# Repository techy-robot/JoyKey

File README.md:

---
modified: 2025-02-20T21:09:22-07:00
---
# JoyKey
This is a small macropad that simultaneously acts as game controller and an entertainment device. 

The name is inspired by the Nintendo JoyCon portmanteau (Joystick Controller) except I have replaced the 2nd word with "Keypad" (Joystick Keypad). See [name ideas](name%20ideas.md) for other things I came up with.

My main repo were development will continue: https://github.com/techy-robot/JoyKey

# Features
- Customizable macro pad using QMK firmware
- Game controller mimicking a joy-con
- Offline games that can be played on the display with no connections
- Small handheld size
- Linear keys

# Approoved Parts BOM
- 8 Cherry mx Red keys with clear shell variant
- 8 Black keycaps
- 128x64 px SSD1306-based monochrome display near the top
- SEEED Xiao RP2040 (can be replaced later w/ SEEED xiao MG24 or nRF52840 Sense for BLE and other goodies)
- 12 Sk6812 Mini-E reverse mount RGB leds
- 3 M3x16 screws and M3 heatsets

# Extra Parts BOM
- 1 Analog PS2 Joystick (I already have)
- 1 Alps SRBE110301. (flat volume dial on the side). LCSC #C160861
- AP2112K-3.3 Linear Regulator. LCSC #C51118
- MCP73831T-2ACI/OT Lipo Battery Charger. LCSC #C424093
- 4 10uf 0805 capacitors. LCSC #C15850
- DMG3415 Sot23-3 PMOS. LCSC #C7202986
- 3 10k 0805 resistors. LCSC #C17414
- 1 2k 0805 resistor. LCSC #C17604
- 1 0603 LED. LCSC #C2286
- 1 LSM6DS3 LCSC #C967633
- JST PH S2B smd LCSC #C295747
- 12 1N4148W diodes LCSC #C2128
- 1 MBR0540 schotkey LCSC #C78545

# Pictures

## Case

## PCB
Bottom

Top

## Schematic

# Sprite Credit

All icons that are converted using qmk's command line tool were originally from Nikoichu's 1-bit Pixel Icons set, which is licensed CC0 1.0

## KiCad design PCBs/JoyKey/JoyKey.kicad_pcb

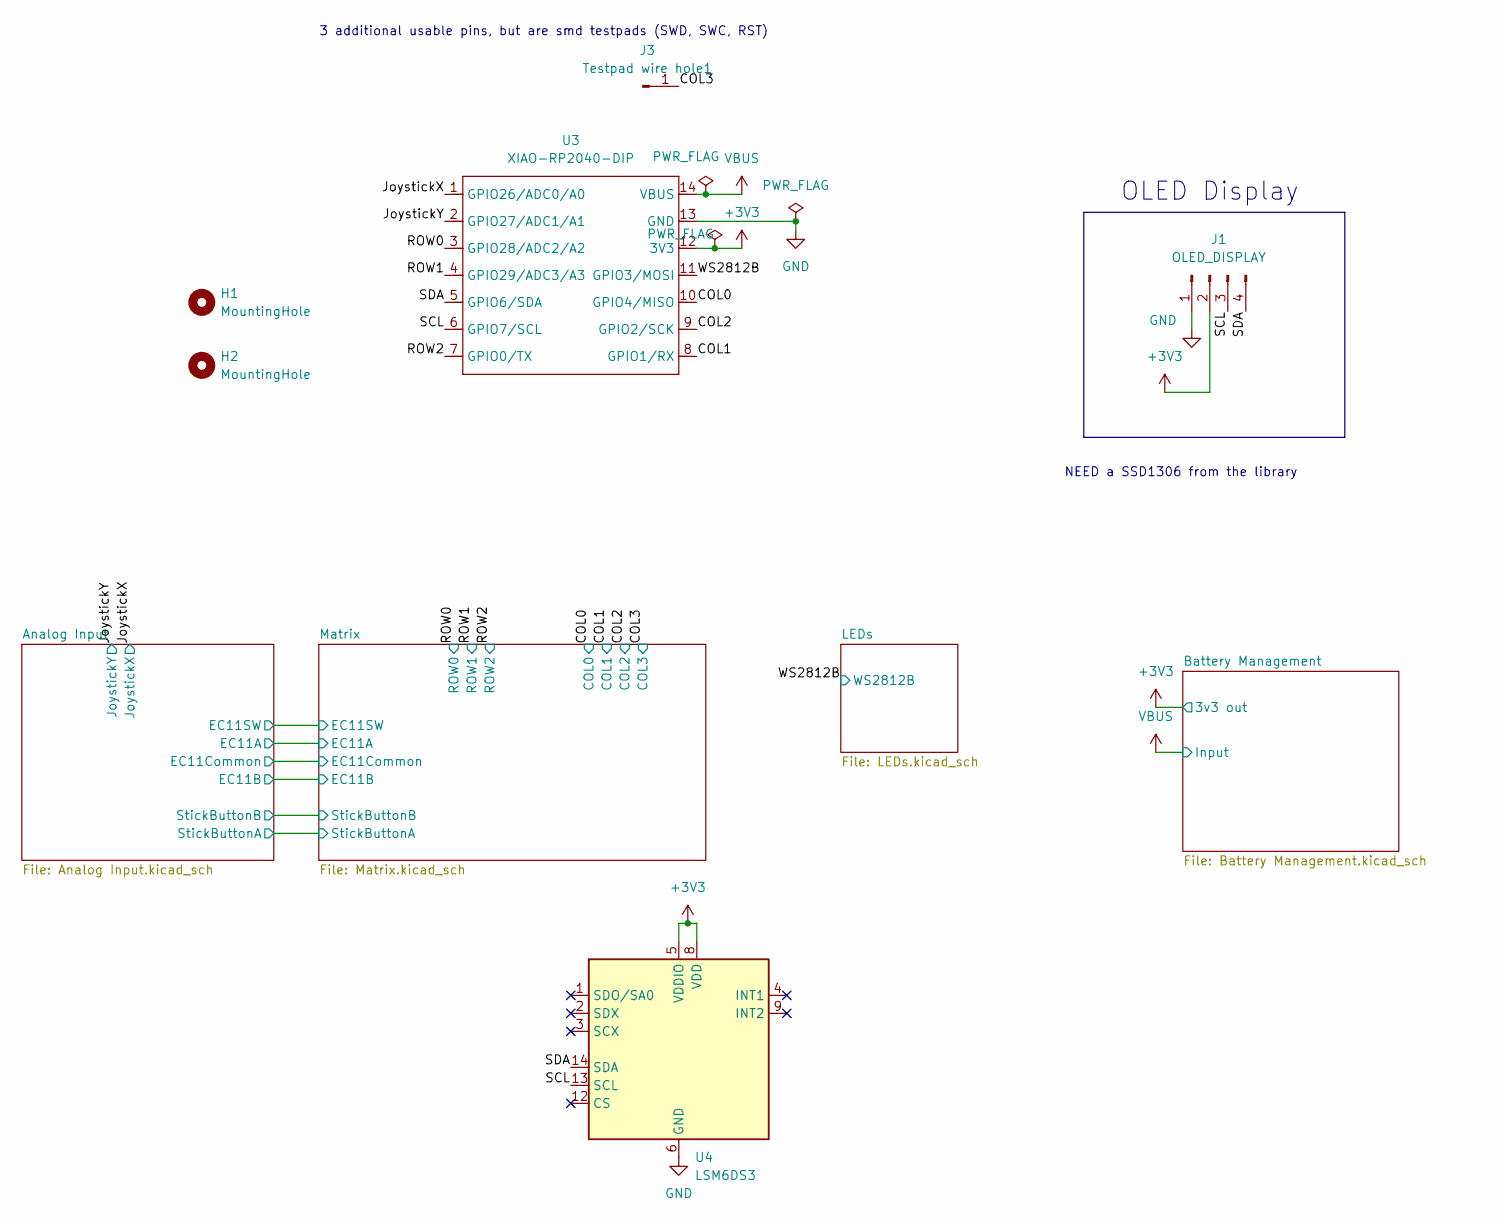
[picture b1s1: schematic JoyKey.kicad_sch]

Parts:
H1, H2: MountingHole; MountingHole_3.2mm_M3_Pad
J1: OLED_DISPLAY; SSD1306-OLED096-128x64
J3: Testpad wire hole1; PinHeader_1x01_P2.54mm_Vertical
U3: XIAO-RP2040-DIP
U4: LSM6DS3; LGA-14_3x2.5mm_P0.5mm_LayoutBorder3x4y_COSTSAVERPADs; LCSC C967633

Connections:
+3V3: J1.2, U3.12 (3V3), U4.5 (VDDIO), U4.8 (VDD); also elsewhere on the board
/COL0: U3.10 (GPIO4/MISO); also elsewhere on the board
/COL1: U3.8 (GPIO1/RX); also elsewhere on the board
/COL2: U3.9 (GPIO2/SCK); also elsewhere on the board
/COL3: J3.1; also elsewhere on the board
/JoystickX: U3.1 (GPIO26/ADC0/A0); also elsewhere on the board
/JoystickY: U3.2 (GPIO27/ADC1/A1); also elsewhere on the board
/ROW0: U3.3 (GPIO28/ADC2/A2); also elsewhere on the board
/ROW1: U3.4 (GPIO29/ADC3/A3); also elsewhere on the board
/ROW2: U3.7 (GPIO0/TX); also elsewhere on the board
/SCL: J1.3, U3.6 (GPIO7/SCL), U4.13 (SCL)
/SDA: J1.4, U3.5 (GPIO6/SDA), U4.14 (SDA)
/WS2812B: U3.11 (GPIO3/MOSI); also elsewhere on the board
GND: J1.1, U3.13 (GND), U4.6 (GND), U4.7 (GND); also elsewhere on the board
VBUS: U3.14 (VBUS); also elsewhere on the board

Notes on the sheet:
NEED a SSD1306 from the library
OLED Display
3 additional usable pins, but are smd testpads (SWD, SWC, RST)

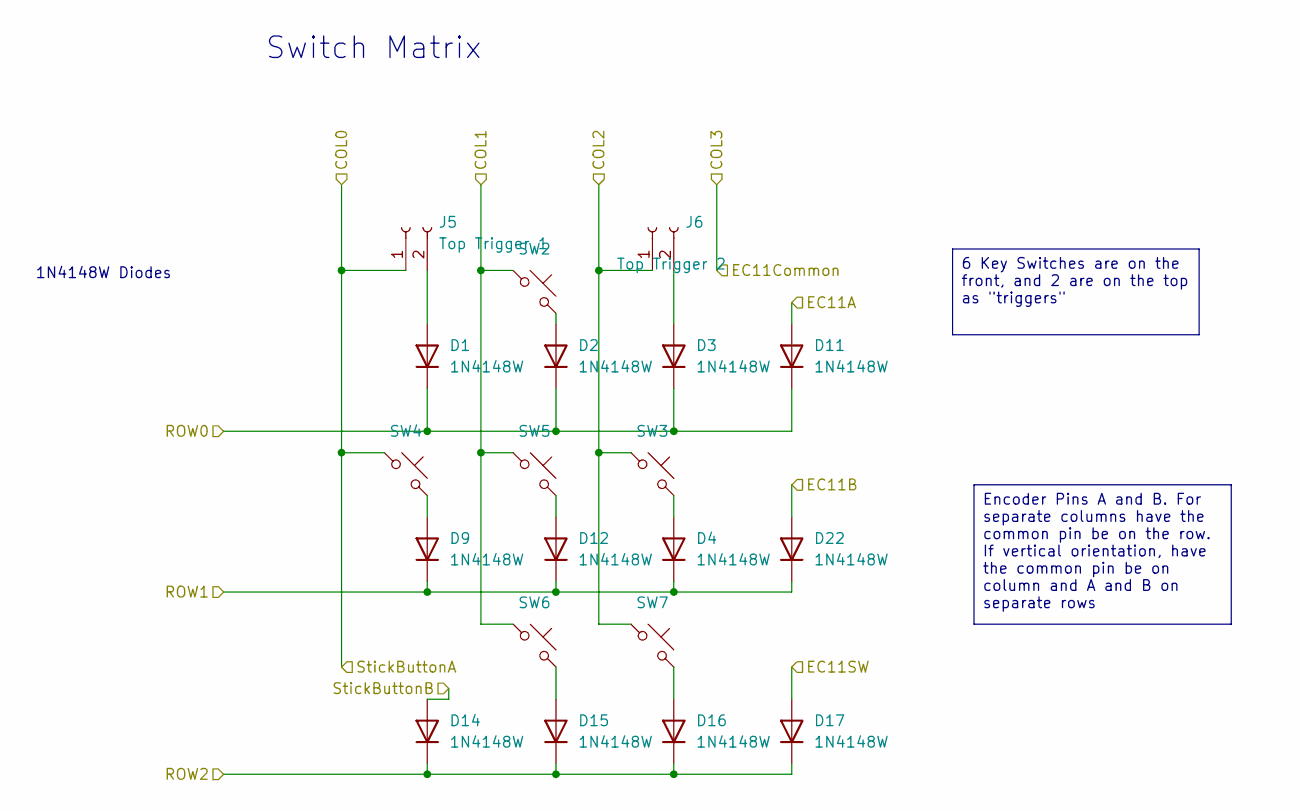
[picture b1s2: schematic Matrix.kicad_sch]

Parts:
D1, D2, D3, D4, D9, D11, D12, D14, D15, D16, D17, D22: 1N4148W; Nexperia_CFP3_SOD-123W; LCSC C2128
J5: Top Trigger 1; PinHeader_1x02_P2.54mm_Vertical
J6: Top Trigger 2; PinHeader_1x02_P2.54mm_Vertical
SW2, SW3, SW4, SW5, SW6, SW7: SW_Push_45deg; MX-Solderable-1U

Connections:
/Analog Input/EC11A: D11.2 (A); also elsewhere on the board
/Analog Input/EC11B: D22.2 (A); also elsewhere on the board
/Analog Input/EC11SW: D17.2 (A); also elsewhere on the board
/Analog Input/StickButtonB: D14.2 (A); also elsewhere on the board
/COL0: J5.1, SW4.1; also elsewhere on the board
/COL1: SW2.1, SW5.1, SW6.1; also elsewhere on the board
/COL2: J6.1, SW3.1, SW7.1; also elsewhere on the board
/ROW0: D1.1 (K), D2.1 (K), D3.1 (K), D11.1 (K); also elsewhere on the board
/ROW1: D4.1 (K), D9.1 (K), D12.1 (K), D22.1 (K); also elsewhere on the board
/ROW2: D14.1 (K), D15.1 (K), D16.1 (K), D17.1 (K); also elsewhere on the board
unnamed: D1.2 (A), J5.2
unnamed: D2.2 (A), SW2.2
unnamed: D3.2 (A), J6.2
unnamed: D4.2 (A), SW3.2
unnamed: D9.2 (A), SW4.2
unnamed: D12.2 (A), SW5.2
unnamed: D15.2 (A), SW6.2
unnamed: D16.2 (A), SW7.2

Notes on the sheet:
Switch Matrix
1N4148W Diodes
Encoder Pins A and B. For separate columns have the common pin be on the row. If vertical orientation, have the common pin be on column and A and B on separate rows
6 Key Switches are on the front, and 2 are on the top as "triggers"

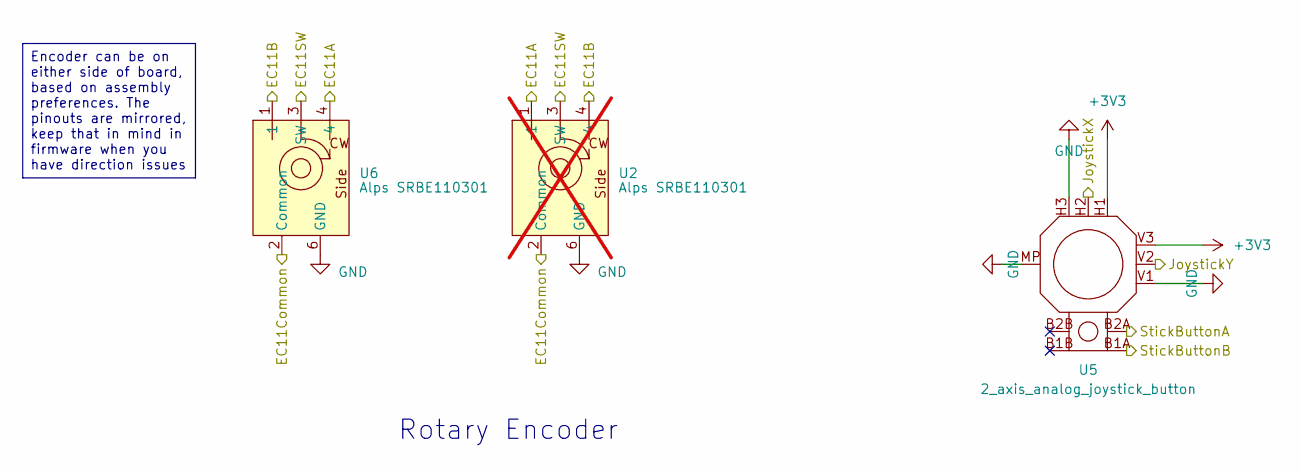
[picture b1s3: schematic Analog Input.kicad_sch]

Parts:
U2: Alps SRBE110301; not fitted
U5: 2_axis_analog_joystick_button; Adafruit 2-Axis joystick
U6: Alps SRBE110301

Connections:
+3V3: U5.H1, U5.V3; also elsewhere on the board
/Analog Input/EC11A: U2.1, U6.4; also elsewhere on the board
/Analog Input/EC11B: U2.4, U6.1; also elsewhere on the board
/Analog Input/EC11SW: U2.3 (SW), U6.3 (SW); also elsewhere on the board
/Analog Input/StickButtonB: U5.B1A; also elsewhere on the board
/COL0: U5.B2A; also elsewhere on the board
/COL3: U2.2 (Common), U6.2 (Common); also elsewhere on the board
/JoystickX: U5.H2; also elsewhere on the board
/JoystickY: U5.V2; also elsewhere on the board
GND: U2.5 (GND), U2.6 (GND), U5.H3, U5.MP, U5.V1, U6.5 (GND), U6.6 (GND); also elsewhere on the board

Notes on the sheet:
Rotary Encoder
Encoder can be on either side of board, based on assembly preferences. The pinouts are mirrored, keep that in mind in firmware when you have direction issues

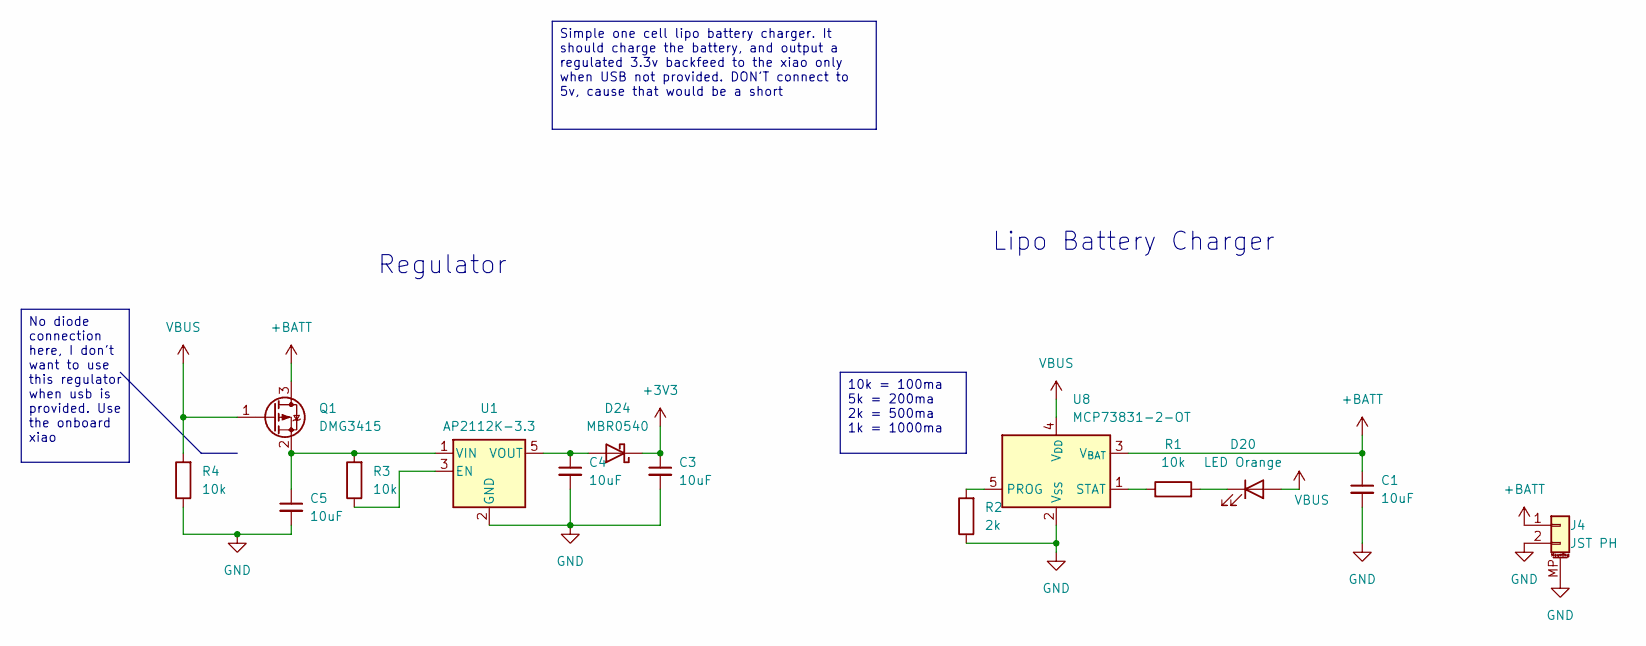
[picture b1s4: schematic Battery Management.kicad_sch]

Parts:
C1, C3, C4, C5: 10uF; C_0805_2012Metric; LCSC C15850
D20: LED Orange; LED_0603_1608Metric; LCSC C2286
D24: MBR0540; Nexperia_CFP3_SOD-123W; LCSC C78545
J4: JST PH; JST_PH_S2B-PH-SM4-TB_1x02-1MP_P2.00mm_Horizontal; LCSC C295747
Q1: DMG3415; SOT-23-3; LCSC C7202986
R1, R3, R4: 10k; R_0805_2012Metric; LCSC C17414
R2: 2k; R_0805_2012Metric; LCSC C17604
U1: AP2112K-3.3; SOT-23-5; LCSC C51118
U8: MCP73831-2-OT; SOT-23-5; LCSC C424093

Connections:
+3V3: C3.1, D24.1 (K); also elsewhere on the board
+BATT: C1.1, J4.1, Q1.3 (D), U8.3 (V_{BAT})
GND: C1.2, C3.2, C4.2, C5.2, J4.2, J4.MP (MountPin), R2.1, R4.1, U1.2 (GND), U8.2 (V_{SS}); also elsewhere on the board
unnamed: D20.1 (K), R1.2
unnamed: C4.1, D24.2 (A), U1.5 (VOUT)
unnamed: C5.1, Q1.2 (S), R3.2, U1.1 (VIN)
unnamed: R3.1, U1.3 (EN)
unnamed: R2.2, U8.5 (PROG)
unnamed: R1.1, U8.1 (STAT)
VBUS: D20.2 (A), Q1.1 (G), R4.2, U8.4 (V_{DD}); also elsewhere on the board

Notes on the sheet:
Lipo Battery Charger
Regulator
10k = 100ma 5k = 200ma 2k = 500ma 1k = 1000ma
No diode connection here, I don't want to use this regulator when usb is provided. Use the onboard xiao
Simple one cell lipo battery charger. It should charge the battery, and output a regulated 3.3v backfeed to the xiao only when USB not provided. DON'T connect to 5v, cause that would be a short

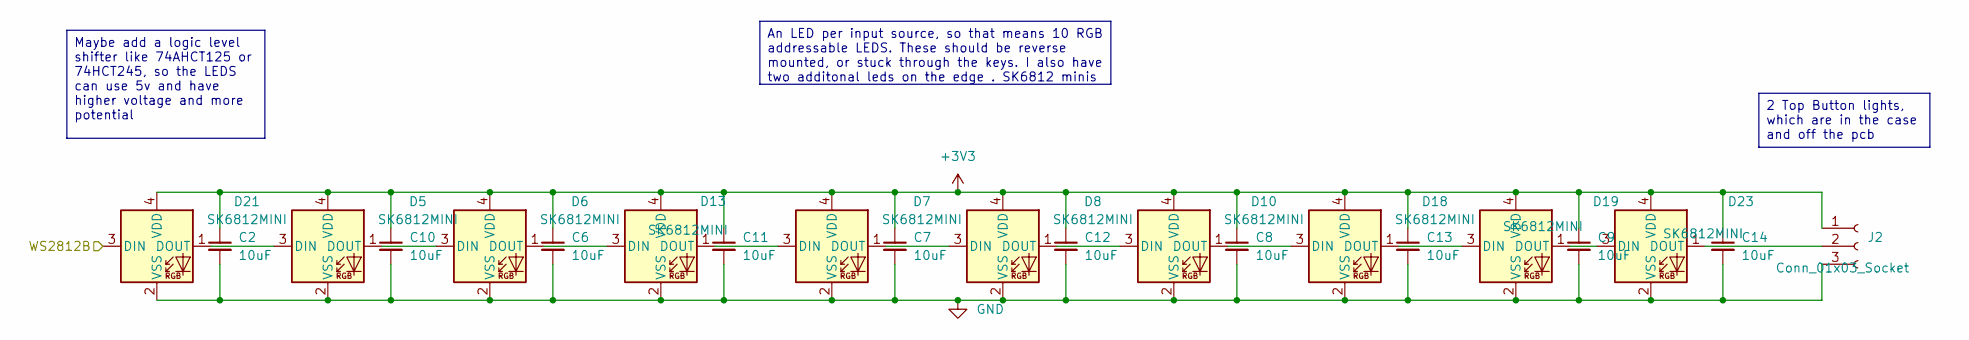
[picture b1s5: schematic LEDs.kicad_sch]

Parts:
C2, C6, C7, C8, C9, C10, C11, C12, C13, C14: 10uF; C_0805_2012Metric; LCSC C15850
D5, D6, D7, D8, D10, D13, D18, D19, D21, D23: SK6812MINI; SK6812MINI-E
J2: Conn_01x03_Socket; PinHeader_1x03_P2.54mm_Vertical

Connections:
+3V3: C2.1, C6.1, C7.1, C8.1, C9.1, C10.1, C11.1, C12.1, C13.1, C14.1, D5.4 (VDD), D6.4 (VDD), D7.4 (VDD), D8.4 (VDD), D10.4 (VDD), D13.4 (VDD), D18.4 (VDD), D19.4 (VDD), D21.4 (VDD), D23.4 (VDD), J2.1; also elsewhere on the board
/WS2812B: D21.3 (DIN); also elsewhere on the board
GND: C2.2, C6.2, C7.2, C8.2, C9.2, C10.2, C11.2, C12.2, C13.2, C14.2, D5.2 (VSS), D6.2 (VSS), D7.2 (VSS), D8.2 (VSS), D10.2 (VSS), D13.2 (VSS), D18.2 (VSS), D19.2 (VSS), D21.2 (VSS), D23.2 (VSS), J2.3; also elsewhere on the board
unnamed: D5.1 (DOUT), D6.3 (DIN)
unnamed: D7.1 (DOUT), D8.3 (DIN)
unnamed: D8.1 (DOUT), D10.3 (DIN)
unnamed: D10.1 (DOUT), D18.3 (DIN)
unnamed: D6.1 (DOUT), D13.3 (DIN)
unnamed: D7.3 (DIN), D13.1 (DOUT)
unnamed: D18.1 (DOUT), D19.3 (DIN)
unnamed: D19.1 (DOUT), D23.3 (DIN)
unnamed: D5.3 (DIN), D21.1 (DOUT)
unnamed: D23.1 (DOUT), J2.2

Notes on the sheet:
2 Top Button lights, which are in the case and off the pcb
An LED per input source, so that means 10 RGB addressable LEDS. These should be reverse mounted, or stuck through the keys. I also have two additonal leds on the edge . SK6812 minis
Maybe add a logic level shifter like 74AHCT125 or 74HCT245, so the LEDS can use 5v and have higher voltage and more potential

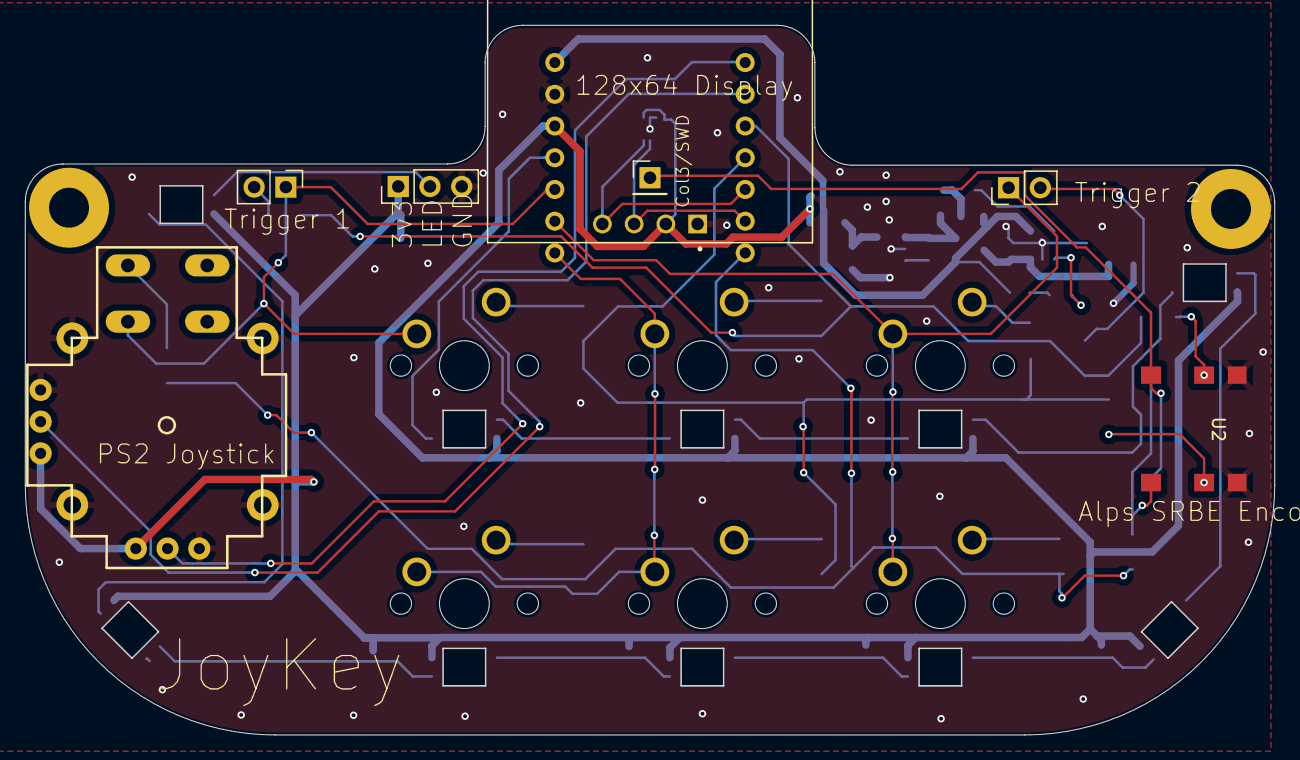
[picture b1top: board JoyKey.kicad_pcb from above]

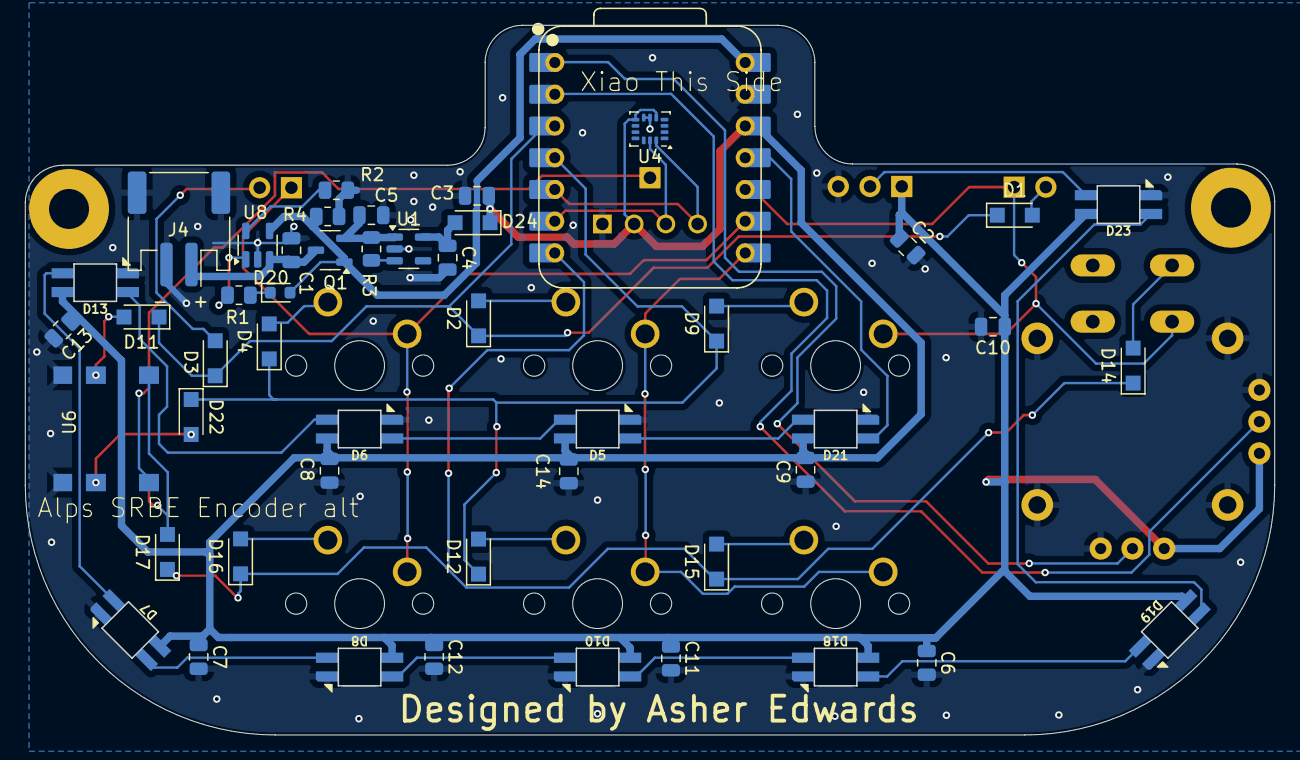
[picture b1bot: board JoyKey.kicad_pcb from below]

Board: 2 copper layers, 100.0 x 56.8 mm, 64 parts (49 on the bottom side), 44 nets.

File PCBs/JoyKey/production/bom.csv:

Designator,Footprint,Quantity,Value,LCSC Part #
"C1, C10, C11, C12, C13, C14, C2, C3, C4, C5, C6, C7, C8, C9",0805,14,10uF,C15850
"D1, D11, D12, D14, D15, D16, D17, D2, D22, D3, D4, D9",Nexperia_CFP3_SOD-123W,12,1N4148W,C2128
"D10, D13, D18, D19, D21, D23, D5, D6, D7, D8",SK6812MINI-E,10,SK6812MINI,
D20,0603,1,LED Orange,C2286
D24,Nexperia_CFP3_SOD-123W,1,MBR0540,C78545
J1,SSD1306-OLED096-128x64,1,OLED_DISPLAY,
J2,PinHeader_1x03_P2.54mm_Vertical,1,Conn_01x03_Socket,
J3,PinHeader_1x01_P2.54mm_Vertical,1,Testpad wire hole1,
J4,JST_PH_S2B-PH-SM4-TB_1x02-1MP_P2.00mm_Horizontal,1,JST PH,C295747
J5,PinHeader_1x02_P2.54mm_Vertical,1,Top Trigger 1,
J6,PinHeader_1x02_P2.54mm_Vertical,1,Top Trigger 2,
Q1,SOT-23-3,1,DMG3415,C7202986
"R1, R3, R4",0805,3,10k,C17414
R2,0805,1,2k,C17604
"SW2, SW3, SW4, SW5, SW6, SW7",MX-Solderable-1U,6,SW_Push_45deg,
U1,SOT-23-5,1,AP2112K-3.3,C51118
U3,XIAO-RP2040-DIP,1,XIAO-RP2040-DIP,
U4,LGA-14_3x2.5mm_P0.5mm_LayoutBorder3x4y_COSTSAVERPADs,1,LSM6DS3,C967633
U5,Adafruit 2-Axis joystick,1,2_axis_analog_joystick_button,
U6,Alps SRBE110301,1,Alps SRBE110301,
U8,SOT-23-5,1,MCP73831-2-OT,C424093

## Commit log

2025-02-12 Add draft schematics for all the input sources
2025-02-14 Removed unnecessary library
    I have added the library to my local library, but I don't need it in my repo.
2025-02-14 Updated matrix for encoder
    I swapped the common pin on the encoder to be connected to the columns since my scanning will be col2row. I don't want the common to go through two diodes!
2025-02-14 Simplified analog input schematic and added proper joystick symbol
2025-02-14 Rearranged LEDs and switched to SK6812 mini -e
    These are reverse mount RGB LEDs that I think would be better to use than the ws2812 leds
2025-02-14 Added battery management
    This is the placeholder circuit taken from one of my robot designs. I need to find cheaper and simpler chips. I do NOT need batter power path management due to the xiao being the source and drain at 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
2025-02-14 Updated top level schem arrangement
2025-02-14 Redrawing hierarchical sheet shapes
2025-02-14 Assigned footprints for batt management
2025-02-14 Added netties to matrix for encoder inputs
    I want the nets to be separate in different areas, so I have added netties
2025-02-14 Fixed bug w reverse orientation of LEDs
2025-02-14 Replaced 2 keys with headers for top Triggers
    Since there are not right angle keys (just buttons), I will use normal keys embedded in the case with wires soldering to the board
2025-02-14 Updated SMD Resistor size to 0805
    I don't want to use small resistors on this project, too much of a hassle.
2025-02-14 Switched output diode to known model
    This is a schottkey diode that I have worked with before and I know its low dropout and quick reacting
2025-02-14 Fixed short between battery gate and ground
2025-02-14 Fixed ERC rules
2025-02-14 Updated Parts in PCB
2025-02-14 Started pcb placement
2025-02-15 Updated Diode to SMD
    I don't want through holes because they take up too much space
2025-02-15 Updated to not distinguished btw LEDs per element
2025-02-15 Updated PCB components
2025-02-15 Updated display to proper one
2025-02-15 Added Mating Point to joystick schematic
2025-02-15 Finished main part layout
2025-02-15 Re-arranged matrix to have L-shaped clusters
    Based on my horizontal layout I really have a 6*2 matrix, however the most switches for the least pins is actually a 4*3. So, I have to great creative with my routing to make it fit.
2025-02-15 Fixed Encoder on Matrix (again)
    I got it messed up, A and B should have separate power sources (columns) and common should go to the row. If I had vertical orientation I would have common be on the column and A and B on separate ro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
2025-02-15 Removed Display Mounting holes
    Annoying, and unneeded
2025-02-16 Revert "Added netties to matrix for encoder inputs"
2025-02-16 Adjusted Edge Cuts shape
2025-02-16 Swapped Col1 and 2 for easier routing
2025-02-16 Finished Column routing and LED Data routing
2025-02-16 Finished Display Routing
2025-02-16 Added Ground Fill
2025-02-16 Swapped row pins for easier routing
2025-02-16 Finished Row routing
2025-02-16 Add Mating point GND to encoder
2025-02-16 Finished 3v3 and Diode routing
2025-02-16 Finished Joystick Routing
2025-02-16 Moved left joystick LED
2025-02-16 Adjusted Edge Lights and increased board size to 100mm
2025-02-16 Adjusted trigger switch position and LED strip header
2025-02-16 Added custom DRC rule to exclude reverse mount edge clearance
    Its in the footprint that the pads are right next to the hole, and it doesn't matter if some copper is cut out.
2025-02-16 Fixed some clearance issues
2025-02-16 Add 2 mounting holes
2025-02-16 Added filleted lines and CAD export
2025-02-16 Added Silkscreen name and author
2025-02-17 Adjusted display to be in PCB center instead of keypad center
    It looks better now, originally I wanted the whole display to be centered for the whole device, but I think I may end up using the verticle encoder and having the pcb be the final shape
2025-02-17 Updated README BOM & added ref pictures
2025-02-17 Added Accel and Gyro sensor
2025-02-18 Adjusted silkscreen text and added custom font
2025-02-20 Added 2 extra LEDs
2025-02-20 Updated readme bom
2025-02-20 Switched encoder to Alps EC12
    I wanted something shorter and that didn't have a metal screw post. I do loose out on the switch though, which I've exposed via a separate header
2025-02-21 Updated Battery Management to Adafruit Feather system
    I wanted to use a proven design that was low cost, and this seemed the best option. Only modification is removing the 5v input to the 3.3v regulator so that I don't have two regulators fighting
2025-02-21 Added JST mating point to connector
2025-02-21 Switched out accel+gyro unit
2025-02-21 Added Complete battery management layout
2025-02-21 Fixed some silkscreen errors
2025-02-21 Changed footprint for Gyro to avoid copper clearance issues
2025-02-21 Added Gerber output
2025-02-21 Initial Firmware
2025-02-21 Updated CAD
2025-03-12 Small tweaks to PCB
2025-03-12 Updated CAD model for more ergonomic position
2025-03-15 Reverse polarity of JST to match Adafruit Battery polarity
    It was an issue I had missed in my review
2025-03-15 Added Pictures
2025-03-15 Updated BOM with LCSC parts
2025-03-17 Added Positive and Negative symbols to JST battery plug
2025-03-17 Switched encoder to Alps SRBE110301 in sch
2025-03-17 Updated to Vertical matrix orientation of encoder
2025-03-17 Fixed all routing and added footprint of encoder
2025-03-17 Fixed Encoder Silkscreen
2025-03-17 Reduce ground differences
2025-03-17 fix DRC errors
2025-03-17 Updated production files
2025-06-29 Add reverse mount for side encoder to simplifiy assembly
    Now, if you want, you can get ALL SMD components on one side! I still prefer the encoder to be put on the top side because it is more central to the whole body, but of course, 2 sided assembly has it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
2025-06-30 Add decoupling capacitors to LEDs
    There isn't much to loose from this
2025-06-30 Added larger battery cavity in CAD
2025-07-11 fixed finger grips, overlaps, and magic numbers
2025-07-11 fix screen holder dimensions
2025-07-11 swap screw & heatset sides
2025-07-11 widened case
2025-07-11 fixed assembly and encoder dial side
2025-07-12 Added dial
2025-07-14 fix screen and key gap
2025-07-14 swap encoder wall w lid
    Now the lid comes on top of the encoder dial to enclose it
2025-07-14 Fix dial & battery compartment
2025-07-14 make bottom fillets print nicer with chamfers
2025-07-15 add lip and hook on front lid
2025-07-16 make case wider and angle finger grips
2025-07-16 add LED ports to case
2025-07-16 Updated assembly
2025-07-16 minor printability tweaks
2025-07-16 changed body shape to be more joycon like
2025-07-16 fix dial and mount
2025-07-16 cutout for capacitor, increase gap for screen wires
2025-07-16 made dial clickable again and increase finger space
2025-07-16 italized text
2025-07-16 fixed corrupted files
2025-07-17 Reorganized firmware
2025-07-17 Remove old unused schematic
2025-07-17 temporary code, not working
2025-07-18 First working firmware
2025-07-18 Added 3D print config
2025-07-22 First working encoder code!
2025-07-24 Initial Via Support
2025-07-24 Remove print statements
2025-07-24 Increase layer count to 8
2025-07-25 Added encoder layer switching and layer indicator
2025-07-25 Remove debug statements
2025-07-25 Designed Proper ASCII art layout
2025-07-25 Enable all RGB effects
2025-07-26 Disable RGB indicator light on RP2040 Xaio on boot
    This is hidden, consumes power, and really is only useful for debugging that I haven't had time to set up.
2025-07-26 Change default 0 layer to mouse actions
    Boot reset is also optional, I have configured it in VIA for layer 15 but that isn't flashed by default.
2025-07-27 Added sleep and RGB timeout
2025-08-14 Added i2c 128x64 Display
2025-08-14 Add 2 more LEDs on trigger switches
    These were initially meant for a different keyboard with ZMK, but I transffered them over here too.
2025-08-22 Added Layer indicator Display text
2025-08-22 Initial support for Quantum Painter
2025-08-22 Removed unused code
2025-08-23 Added custom fonts and test draw using Painter
2025-08-24 Added variable refresh rate
2025-08-24 Remove old OLED code
2025-08-24 Refactor layer display code
2025-09-08 Add layer and key names structure
    Haven't tested, probably won't work
2025-09-09 Updated pictures
2025-09-09 Add ZMK config submodule
2025-11-23 Working test key display
2025-11-23 Fixed bugs, added boot button, Adjusted colors
2025-11-23 Added encoder rollover logic
2025-11-23 Added text truncate
2025-11-23 Fix keycode for latest FW
2025-11-23 Made all layers explicit so layer change btn worked
2025-11-23 Fixed unused code
2025-11-23 Included color header
2025-11-23 Refactor map definition
2025-11-23 Updated map data
2025-11-23 Created settings utilities
2025-11-23 Disabled Via for custom data entry
2025-11-23 Custom Web configurator
2025-11-23 Working live updating and saving data!
2025-11-23 Updated interface for auto populating
2025-11-23 Integrate custom name logic with Via
2025-11-24 Revamp save logic
2025-11-24 Some cleanup
2025-11-24 Refactor settings
2025-11-24 Revamped lighting control
2025-11-24 Bug fixes with setting update, LED index
2025-11-26 Initial VIA protocol support
2025-11-26 Standardized command ids, fixed render bugs
2025-11-26 Bug fix with live update oled
2025-11-26 Faulty LED fix, 1 less
2025-11-26 Refactor code to have proper includes and gaurd
2025-11-26 Added VIA color picker support
2025-11-26 Updated configurater to have color picker
2025-11-27 Added proper key names to configurators
2025-11-27 Added all layer effect names
2025-11-27 Scaled LED positions for accurate anim
2025-11-27 Change Speed to slider input
2025-11-27 Updated GUI methods
2025-11-27 Updated Key press animation
2025-11-27 First working Icon loading test
2025-11-27 Removed old LED layer indicator
2025-11-27 Working image loading and flashing and GUI setup
2025-11-28 Draft AI implementation of USB filesystem
2025-11-28 Fix some keys showing in wrong spots
2025-11-28 Disable pixel padding
2025-11-28 Changed Defaults for layers
2025-11-28 Added Image credit
2025-11-28 Center Icons
2025-11-28 Added new images
2025-11-28 Revert inverting colors
2025-11-28 Fix image loading overflow
    A few weren't being unloaded causing them to not render when layers were switched. This is dynamic now and fits everything else.
